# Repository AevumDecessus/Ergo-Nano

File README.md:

# Ergo-Nano keyboard design

A ergodox/moonlander inspired wireless-first split keyboard design, defined in code with [Ergogen][ergogen].

Utilizes the [nice!nano][nice-nano] for a wireless-first methodology. The wireless firmware is built on [ZMK][zmk].

[Changelog](./CHANGELOG.md)

## Important notes

This layout is fully generated, and as of the 0.5.0 release HAS NOT BEEN BUILT OR TESTED YET. Feel free to use this as a reference, but you are making this at your own risk until it has been built, tested, and vetted.

`v0.5.1` PCBs have been ordered, build guide and validation results to be added when received/vetted.

## Layout

Replaced all the 1.5U keys with 1U keys on the farthest outside rows, moved the thumb cluster closer to the natural thumb resting location, a major complaint with the Ergodox.

Each half is a 5x7 matrix (with the modifier keys removed from the innermost 2 columns, for 33 main keys) plus 5 thumb keys (38 keys total per side).

Built with MX keysizes by default. Switches are oriented **north-facing (top-lit)** for better shine-through keycap legend illumination; uniform/non-Cherry profiles (such as XDA, DSA, OEM, SA, or MT3) are recommended, as standard Cherry-profile keycaps can interfere with standard-pole MX housings in a north-facing orientation.

### Optional Jumpers

2 pairs of optional jumpers are located to the left of the MCU (`LEDd`/`LEDp` on the front, `ENC1`/`ENC2` on the back) to choose between per-key and underglow LEDs, or the rotary encoder located below the main board. Connect the pair you would like with solder bridges to route `P0` and `P4` to either the LED data/MOSFET gate (`LEDd`/`LEDp`) or the encoder's rotary pins (`ENC1`/`ENC2`).

### Hardware requirements

#### Required hardware (per side)

- [nice!nano][nice-nano]
- 38 MX compatible switches per side
- 38 [Kailh hotswap sockets][hotswap-socket]
- 38-39 SOD-123 (SMD) or 1N4148 (THT) Diodes (1 extra for optional encoder or LED MOSFET gate protection)
- 37-39 1U MX compatible keycaps
  - optional 1.5U vertical keycap for the top of the thumb cluster
  - optional 1U switch in place of optional encoder
- [JST-PH socket][jst]
- [Power Switch][power]
- Battery
  - [Fits under MCU][battery-small] - not recommended with LEDs
  - Larger 3.7V batteries

#### Optional Hardware (per side)

- [nice!view][nice-view]
- Lights
  - 38 [Per Key LED][LED] SK-6812 MINI-E
  - 9 [Underglow LED][LED] SK-6812 MINI-E
  - 470 ohm 1206 SMD or THT resistor (protect LED data line)
  - 10k ohm 1206 SMD or THT resistor (pull up resistor to make sure LEDs are powered off unless specifically requested)
  - AO3401 SOT-23 P-type mosfet (makes sures LEDs have no phantom power draw)
- EC11 Encoder

## Firmware

Firmware can be compiled via the [Firmware][firmware] accompanying repo.

## Contents

Case STLs:

- [Bottom Case PCB](cases/bottom_case_pcb.stl) 3d Printable case with walls that sit flush with the top of the PCB
- [Bottom Case Switch](cases/bottom_case_switch.stl) 3D Printable case that sits flush with the top of the switchplate
- [Deep Bottom Case](cases/bottom_case_deep.stl) Deep bottom case to accommodate larger batteries for longer lifetime

Plates:

- [Backplate](outlines/backplate.dxf) DXF to cut your own backplate out of acrylic/wood/etc
- [Backplate PCB](gerbers/backplate.zip) Gerber release to get a backplate manufactured out of PCB
- [Switchplate](outlines/switchplate.dxf) DXF to cut your own switchplate out of acrylic/wood/etc
- [Switchplate PCB](gerbers/switchplate.zip) Gerber release to get a switchplate manufactured out of PCB

## Images

### Top (Left Hand)

### Bottom (Right Hand)

[battery-small]: https://typeractive.xyz/products/lithium-battery-110mah
[ergogen]: https://github.com/ergogen/ergogen
[firmware]: https://github.com/AevumDecessus/zmk-keyboard-ergonano
[hotswap-socket]: https://typeractive.xyz/products/hotswap-sockets
[jst]: https://typeractive.xyz/products/battery-jack
[LED]: https://keeb.io/products/sk-6812-mini-e-rgb-leds-12-pack
[nice-nano]: https://nicekeyboards.com/nice-nano/
[nice-view]: https://nicekeyboards.com/nice-view/
[power]: https://typeractive.xyz/products/power-switch
[zmk]: https://zmk.dev/

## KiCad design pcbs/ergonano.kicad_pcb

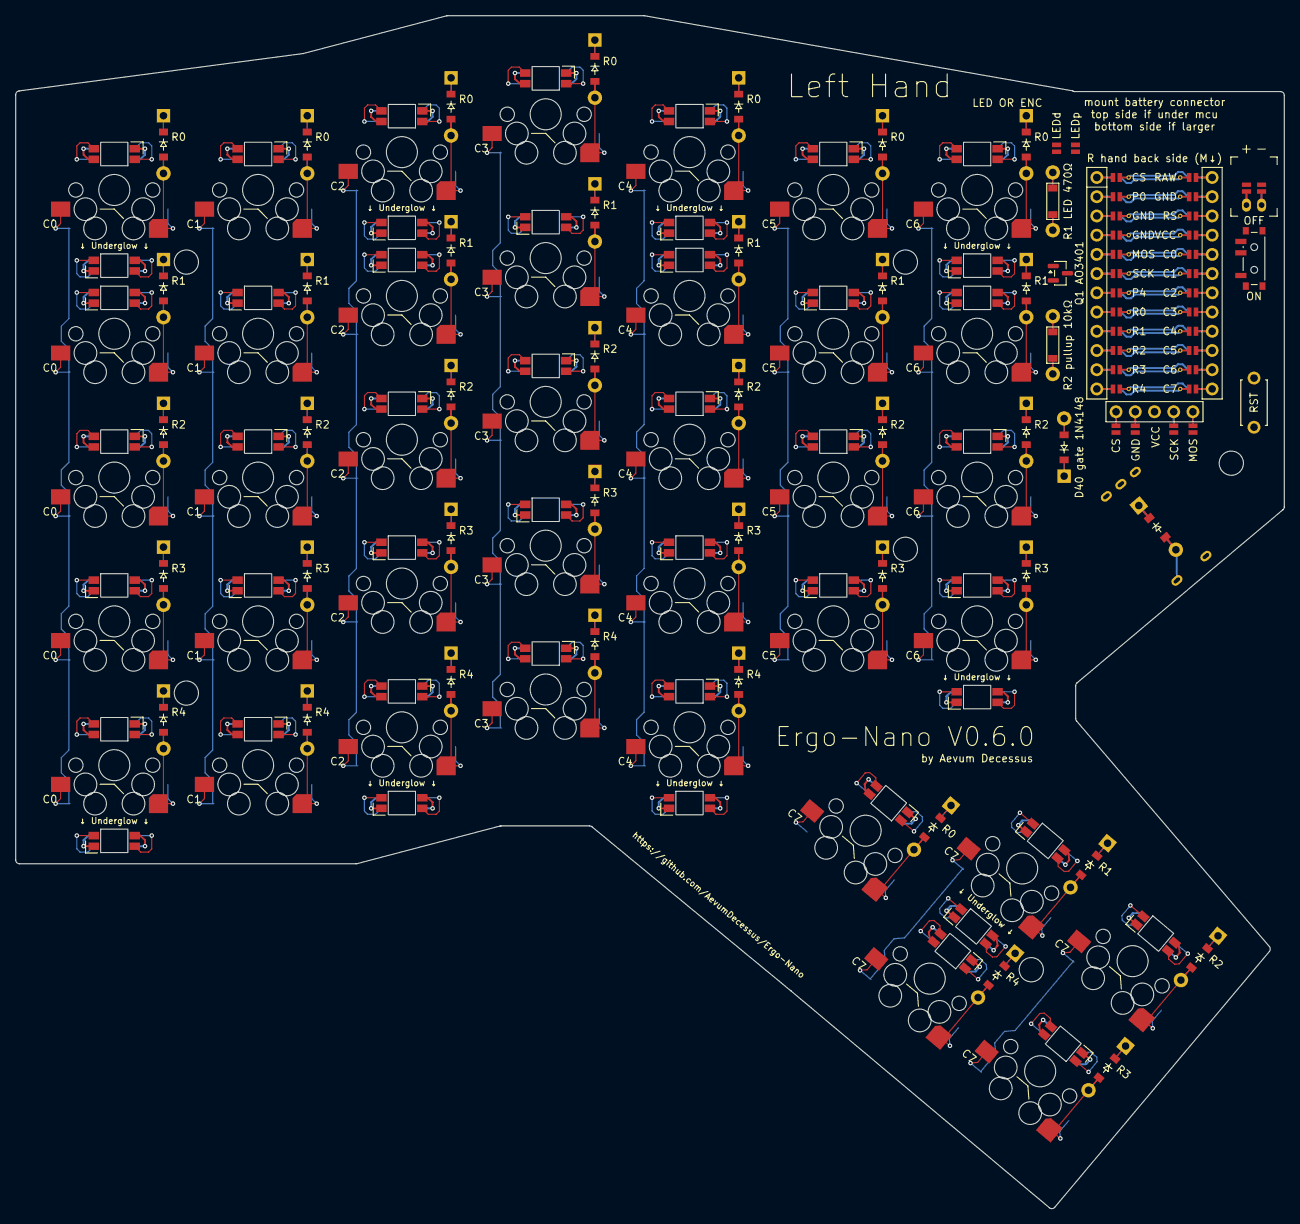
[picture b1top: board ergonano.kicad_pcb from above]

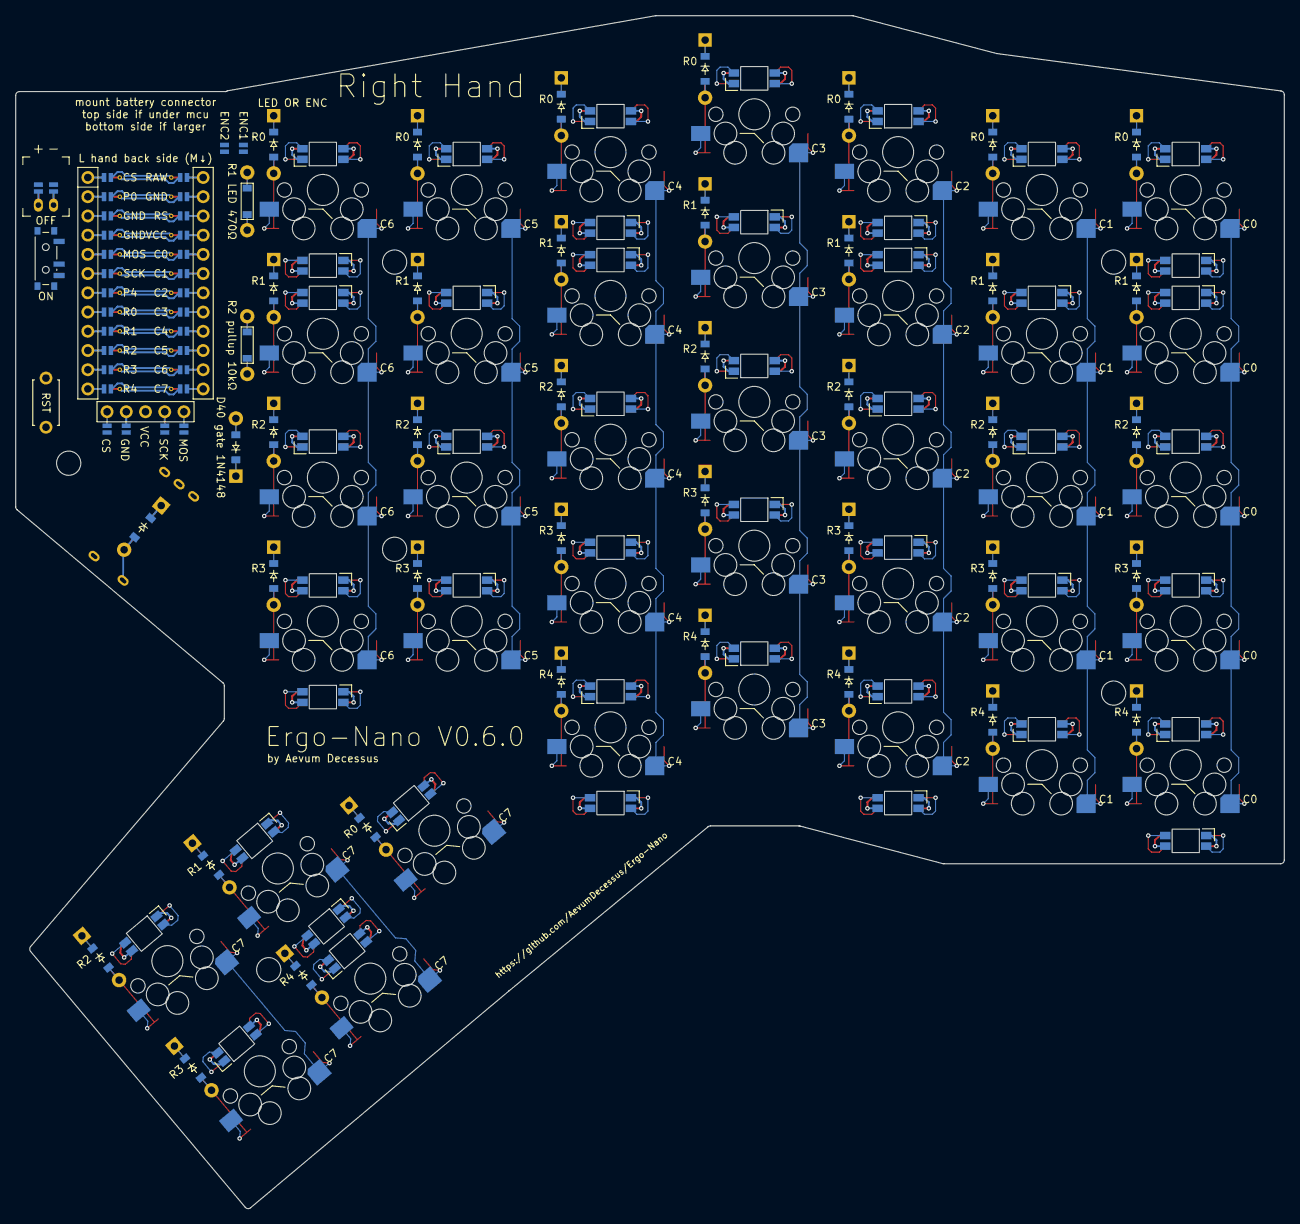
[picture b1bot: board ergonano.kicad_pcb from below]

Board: 2 copper layers, 167.6 x 157.6 mm, 144 parts (87 on the bottom side), 121 nets.

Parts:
D1, D2, D3, D4, D5, D6, D7, D8, D9, D10, D11, D12, D13, D14, D15, D16, D17, D18, D19, D20, D21, D22, D23, D24, D25, D26, D27, D28, D29, D30, D31, D32, D33, D34, D35, D36, D37, D38, D39, D40: diode_tht_sod123
DISP1: display_nice_view
J1, J2, J3, J4: jumper
JST1: battery_connector_jst_ph_2
LED1, LED2, LED3, LED4, LED5, LED6, LED7, LED8, LED9, LED10, LED11, LED12, LED13, LED14, LED15, LED16, LED17, LED18, LED19, LED20, LED21, LED22, LED23, LED24, LED25, LED26, LED27, LED28, LED29, LED30, LED31, LED32, LED33, LED34, LED35, LED36, LED37, LED38, LED39, LED40, LED41, LED42, LED43, LED44, LED45, LED46, LED47: led_SK6812mini-e (per-key, reversible)
MCU1: mcu_nice_nano
MH1, MH2, MH3, MH4, MH5, MH6: mounting_hole_npth
PWR1: power_switch_smd_side
Q1: SOT-23
R1, R2: resistor_tht_1206
RE1: rotary_encoder_ec11_ec12
RST1: reset_switch_tht_top
S1, S2, S3, S4, S5, S6, S7, S8, S9, S10, S11, S12, S13, S14, S15, S16, S17, S18, S19, S20, S21, S22, S23, S24, S25, S26, S27, S28, S29, S30, S31, S32, S33, S34, S35, S36, S37, S38: switch_mx

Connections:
BAT_P: JST1.1, PWR1.1, PWR1.3
C0: MCU1.105, S1.1, S1.2, S2.1, S2.2, S3.1, S3.2, S4.1, S4.2, S5.1, S5.2
C1: MCU1.106, S6.1, S6.2, S7.1, S7.2, S8.1, S8.2, S9.1, S9.2, S10.1, S10.2
C2: MCU1.107, S11.1, S11.2, S12.1, S12.2, S13.1, S13.2, S14.1, S14.2, S15.1, S15.2
C3: MCU1.108, S16.1, S16.2, S17.1, S17.2, S18.1, S18.2, S19.1, S19.2, S20.1, S20.2
C4: MCU1.109, S21.1, S21.2, S22.1, S22.2, S23.1, S23.2, S24.1, S24.2, S25.1, S25.2
C5: MCU1.110, S26.1, S26.2, S27.1, S27.2, S28.1, S28.2, S29.1, S29.2
C6: MCU1.111, RE1.S1, S30.1, S30.2, S31.1, S31.2, S32.1, S32.2, S33.1, S33.2
C7: MCU1.112, S34.1, S34.2, S35.1, S35.2, S36.1, S36.2, S37.1, S37.2, S38.1, S38.2
CS: DISP1.10, DISP1.20, MCU1.124
DISP1_1: DISP1.1, DISP1.14, DISP1.27
DISP1_2: DISP1.2, DISP1.15, DISP1.26
DISP1_4: DISP1.4, DISP1.16, DISP1.25
DISP1_5: DISP1.5, DISP1.17, DISP1.24
E1: J3.2, RE1.A
E2: J4.2, RE1.C
GND: DISP1.11, DISP1.21, JST1.2, LED1.3, LED2.3, LED3.3, LED4.3, LED5.3, LED6.3, LED7.3, LED8.3, LED9.3, LED10.3, LED11.3, LED12.3, LED13.3, LED14.3, LED15.3, LED16.3, LED17.3, LED18.3, LED19.3, LED20.3, LED21.3, LED22.3, LED23.3, LED24.3, LED25.3, LED26.3, LED27.3, LED28.3, LED29.3, LED30.3, LED31.3, LED32.3, LED33.3, LED34.3, LED35.3, LED36.3, LED37.3, LED38.3, LED39.3, LED40.3, LED41.3, LED42.3, LED43.3, LED44.3, LED45.3, LED46.3, LED47.3, MCU1.102, MCU1.121, MCU1.122, RE1.B, RST1.2
JST1_1: JST1.11, JST1.21, JST1.31
JST1_2: JST1.12, JST1.22, JST1.32
J_LED: J1.2, R1.2
J_MFET_GATE: D40.1, J2.2
LED_0: LED19.4, R1.1
LED_1: LED17.4, LED19.2
LED_2: LED15.4, LED17.2
LED_3: LED12.4, LED15.2
LED_4: LED9.4, LED12.2
LED_5: LED6.4, LED9.2
LED_6: LED3.4, LED6.2
LED_7: LED3.2, LED24.4
LED_8: LED24.2, LED26.4
LED_9: LED26.2, LED28.4
LED_10: LED28.2, LED30.4
LED_11: LED30.2, LED32.4
LED_12: LED32.2, LED34.4
LED_13: LED34.2, LED36.4
LED_14: LED18.4, LED36.2
LED_15: LED16.4, LED18.2
LED_16: LED14.4, LED16.2
LED_17: LED11.4, LED14.2
LED_18: LED8.4, LED11.2
LED_19: LED5.4, LED8.2
LED_20: LED2.4, LED5.2
LED_21: LED2.2, LED23.4
LED_22: LED23.2, LED25.4
LED_23: LED25.2, LED27.4
LED_24: LED27.2, LED29.4
LED_25: LED29.2, LED31.4
LED_26: LED31.2, LED33.4
LED_27: LED33.2, LED35.4
LED_28: LED35.2, LED37.4
LED_29: LED37.2, LED38.4
LED_30: LED22.4, LED38.2
LED_31: LED21.4, LED22.2
LED_32: LED20.4, LED21.2
LED_33: LED13.4, LED20.2
LED_34: LED10.4, LED13.2
LED_35: LED7.4, LED10.2
LED_36: LED4.4, LED7.2
LED_37: LED1.4, LED4.2
LED_MFET_GATE: D40.2, Q1.1, R2.1
LED_VCC: LED1.1, LED2.1, LED3.1, LED4.1, LED5.1, LED6.1, LED7.1, LED8.1, LED9.1, LED10.1, LED11.1, LED12.1, LED13.1, LED14.1, LED15.1, LED16.1, LED17.1, LED18.1, LED19.1, LED20.1, LED21.1, LED22.1, LED23.1, LED24.1, LED25.1, LED26.1, LED27.1, LED28.1, LED29.1, LED30.1, LED31.1, LED32.1, LED33.1, LED34.1, LED35.1, LED36.1, LED37.1, LED38.1, LED39.1, LED40.1, LED41.1, LED42.1, LED43.1, LED44.1, LED45.1, LED46.1, LED47.1, Q1.3
MOS: DISP1.13, DISP1.23, MCU1.120
P0: J1.1, J3.1, MCU1.123
P4: J2.1, J4.1, MCU1.118
R0: D5.1, D10.1, D15.1, D20.1, D25.1, D29.1, D33.1, D34.1, MCU1.117
R1: D4.1, D9.1, D14.1, D19.1, D24.1, D28.1, D32.1, D36.1, MCU1.116
R2: D3.1, D8.1, D13.1, D18.1, D23.1, D27.1, D31.1, D38.1, MCU1.115
R3: D2.1, D7.1, D12.1, D17.1, D22.1, D26.1, D30.1, D37.1, MCU1.114
R4: D1.1, D6.1, D11.1, D16.1, D21.1, D35.1, D39.1, MCU1.113
RAW: MCU1.101, PWR1.2, Q1.2, R2.2
RS: MCU1.103, RST1.1
SCK: DISP1.12, DISP1.22, MCU1.119
ULED_1: LED1.2, LED39.4
ULED_2: LED39.2, LED40.4
ULED_3: LED40.2, LED41.4
ULED_4: LED41.2, LED42.4
ULED_5: LED42.2, LED43.4
ULED_6: LED43.2, LED44.4
ULED_7: LED44.2, LED45.4
ULED_8: LED45.2, LED46.4
ULED_9: LED46.2, LED47.4
VCC: DISP1.3, MCU1.104
encoder_encoder: D39.2, RE1.S2
index_bottom: D22.2, S22.1, S22.2
index_home: D23.2, S23.1, S23.2
index_mod: D21.2, S21.1, S21.2
index_num: D25.2, S25.1, S25.2
index_top: D24.2, S24.1, S24.2
inner_bottom: D26.2, S26.1, S26.2
inner_home: D27.2, S27.1, S27.2
inner_num: D29.2, S29.1, S29.2
inner_top: D28.2, S28.1, S28.2
innermod_bottom: D30.2, S30.1, S30.2
innermod_home: D31.2, S31.1, S31.2
innermod_num: D33.2, S33.1, S33.2
innermod_top: D32.2, S32.1, S32.2
middle_bottom: D17.2, S17.1, S17.2
middle_home: D18.2, S18.1, S18.2
middle_mod: D16.2, S16.1, S16.2
middle_num: D20.2, S20.1, S20.2
middle_top: D19.2, S19.1, S19.2
outer_bottom: D2.2, S2.1, S2.2
outer_home: D3.2, S3.1, S3.2
outer_mod: D1.2, S1.1, S1.2
outer_num: D5.2, S5.1, S5.2
outer_top: D4.2, S4.1, S4.2
pinky_bottom: D7.2, S7.1, S7.2
pinky_home: D8.2, S8.1, S8.2
pinky_mod: D6.2, S6.1, S6.2
pinky_num: D10.2, S10.1, S10.2
pinky_top: D9.2, S9.1, S9.2
ring_bottom: D12.2, S12.1, S12.2
ring_home: D13.2, S13.1, S13.2
ring_mod: D11.2, S11.1, S11.2
ring_num: D15.2, S15.1, S15.2
ring_top: D14.2, S14.1, S14.2
t_col0_near: D34.2, S34.1, S34.2
t_col1_far: D36.2, S36.1, S36.2
t_col1_near: D35.2, S35.1, S35.2
t_col2_far: D38.2, S38.1, S38.2
t_col2_near: D37.2, S37.1, S37.2
